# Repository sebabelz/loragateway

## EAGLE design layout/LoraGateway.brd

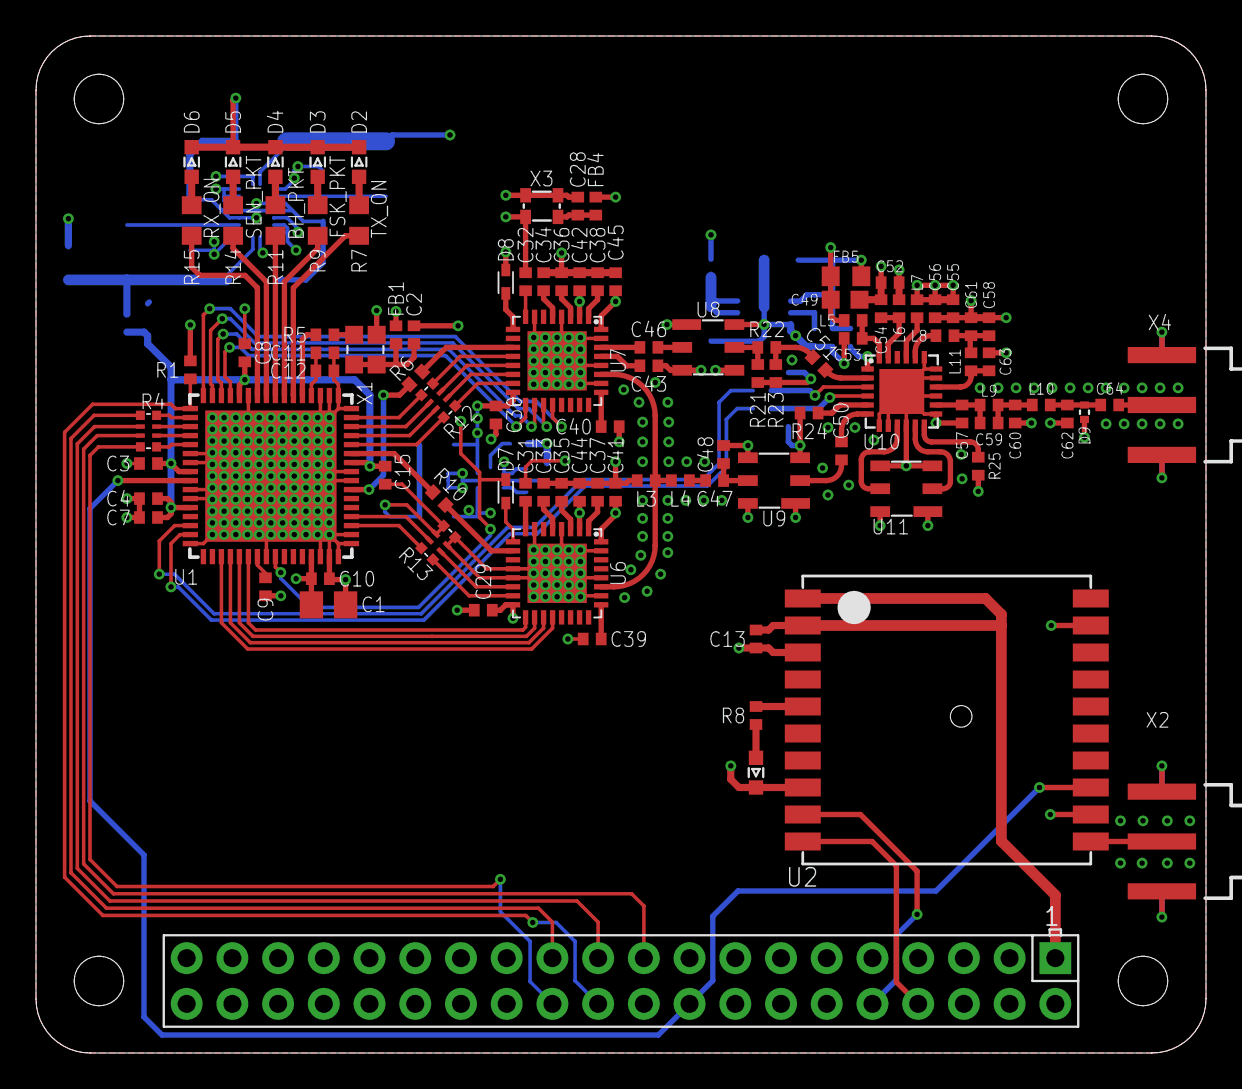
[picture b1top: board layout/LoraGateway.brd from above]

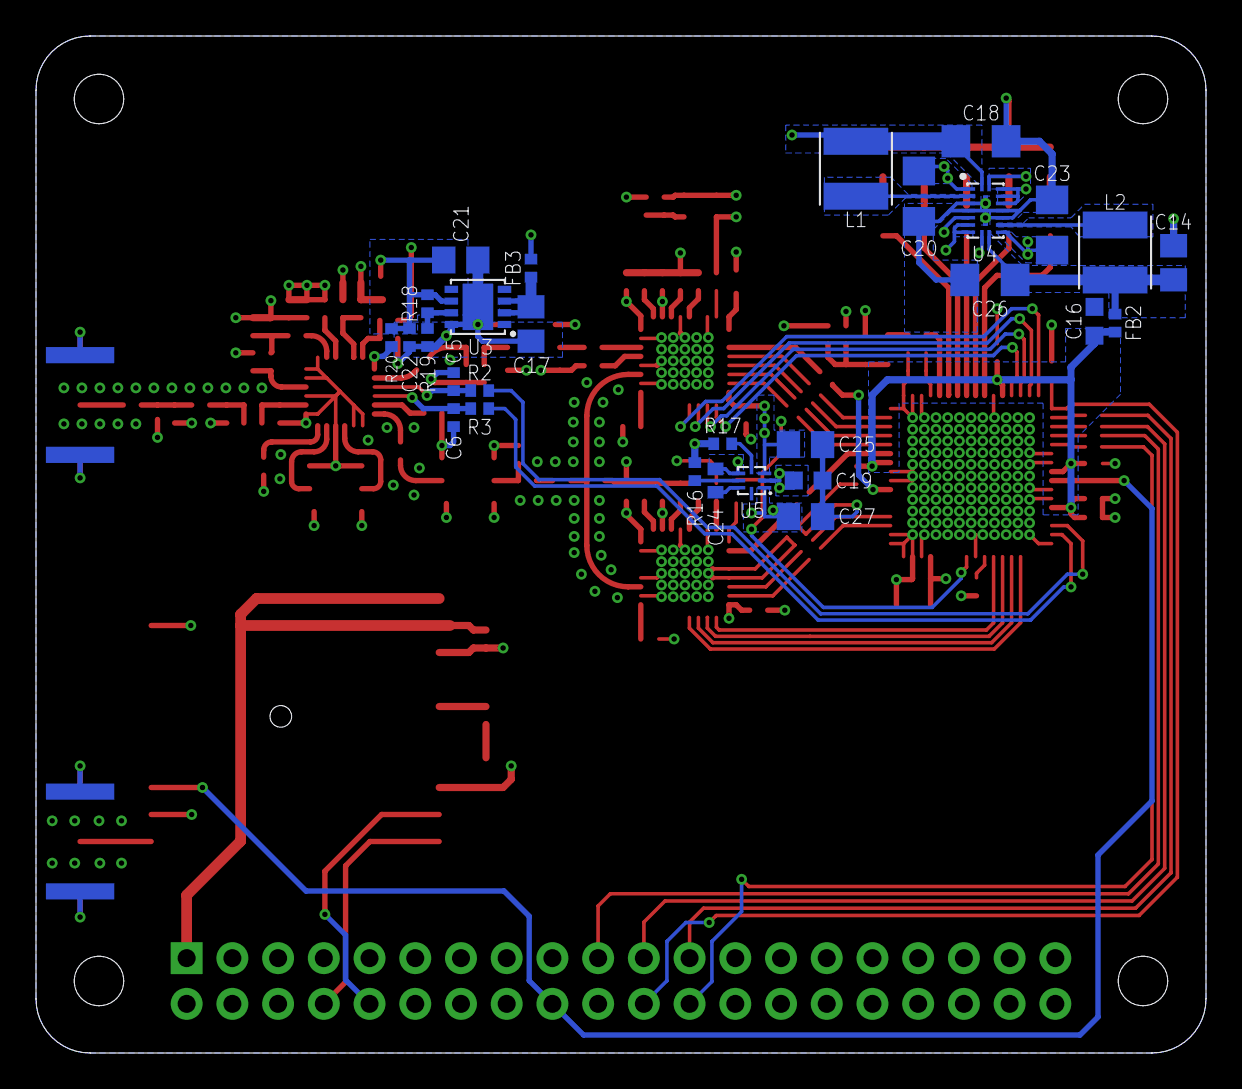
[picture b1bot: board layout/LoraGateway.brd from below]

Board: 4 copper layers, 65.0 x 56.5 mm, 130 parts (29 on the bottom side), 116 nets.

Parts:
C1, C14: 10µF; C0805
C2, C37, C38, C52: 10nF; C0402
C3, C12, C29, C30, C41, C42, C44, C45: 1µF; C0402
C4, C7, C8, C9, C10, C11, C13, C15, C24, C28, C33, C34, C35, C36, C39, C40: 100nF; C0402
C5, C6, C22, C43, C46, C47, C50, C64: 56pF; C0402
C16: 1µF; C0603
C17, C21: 10uF; C0805
C18, C26: 22uF; C1206
C19: 2.2uF; C0603
C20, C23: 10uF; C1206
C25, C27: 1uF; C0805
C31, C32, C55: 1nF; C0402
C48: 5.6pF; C0402
C49: 4.7µF; C0603
C51, C57, C60: 3.3pF; C0402
C53: 150pF; C0402
C54: 22pF; C0402
C56: 33pF; C0402
C58: 7.5pF; C0402
C59: 1.5pF; C0402
C61, C63: 5.1pF; C0402
C62: 2.7pF; C0402
D1, D2, D3, D4, D5, D6: LED; D0603
D7, D8: BAT54XV2T1G; SOD523
D9: LXES15AAA1-153
FB1, FB2, FB3, FB4: L0402
FB5: L0603
J1: RPI-HEADER3B; RPI
L1, L2: 2.2µ; ASPI-0418
L3: 33nH; L0402
L4: 3.9nH; L0402
L5: 3.3nH; L0402
L6: 4.7nH; L0402
L7: 6.8nH; L0402
L8: 2.7nH; L0402
L9, L10: 5.6nH; L0402
L11: 6.2nH; L0402
R1, R16, R17: 10k; R0402
R2, R3, R6, R10, R20: 100; R0402
R4, R12, R13: EXB-N8V101JX; EXB28V
R5: 0; R0402
R7, R9, R11, R14, R15: 470; R0603
R8: 470; R0402
R18: 16k; R0402
R19: 12k; R0402
R21, R23: 300; R0402
R22: 18; R0402
R24, R25: 49R9; R0402
U1: QFN64-9X9
U2: FGPMMOPA6H
U3: 3X3MLPD-8
U4: SC283; 2X3MLPQ-W18
U5: SC560H; MLPQ-UT8
U6, U7: SX1257; QFN32
U8, U9, U11: DCC6C-3X3
U10: SE2435L; VQFN24-4X4
X1: END4825A; 2.5X2.0MM
X2, X4: SMA-KE11; J502-ND-142-0711-871/876
X3: END4263A; 2.0X1.6MM

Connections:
+5V: C19.1, C20.1, C23.1, J1.2, J1.4, R16.1, R17.1, U4.1, U4.5, U4.8, U4.10, U4.14, U4.15, U4.16, U4.17, U5.2
CLKHS: R5.2, U1.53
CLKI: R6.2, U7.11
CLKO_B: R10.2, U6.10
FEM_EN: R20.2, U10.1
GND: C1.2, C2.2, C3.2, C4.2, C5.2, C6.2, C7.2, C8.2, C9.2, C10.2, C11.2, C12.2, C13.2, C14.2, C15.2, C16.2, C17.2, C18.2, C19.2, C20.2, C21.2, C22.2, C23.2, C24.2, C25.2, C26.2, C27.2, C28.2, C29.2, C30.2, C33.1, C34.1, C35.1, C36.1, C37.1, C38.1, C39.2, C40.2, C41.2, C42.2, C43.2, C44.2, C45.2, C48.2, C49.2, C52.2, C53.2, C54.2, C55.2, C56.2, C57.2, C58.2, C60.2, C61.2, C62.2, C63.2, D1.C, D2.C, D3.C, D4.C, D5.C, D6.C, D9.2, J1.6, J1.9, J1.14, J1.20, J1.25, J1.30, J1.34, J1.39, L3.2, R1.1, R13.1, R13.2, R13.7, R13.8, R19.1, R21.2, R23.2, R24.1, R25.1, U1.6, U1.7, U1.10, U1.11, U1.16, U1.24, U1.30, U1.31, U1.32, U1.33, U1.34, U1.40, U1.41, U1.48, U1.49, U1.50, U1.51, U1.59, U1.EXP, U2.3, U2.8, U2.12, U2.19, U3.8, U3.GND, U4.3, U4.4, U4.6, U4.7, U4.12, U4.13, U4.T1, U4.T2, U5.5, U6.4, U6.7, U6.12, U6.13, U6.26, U6.28, U6.31, U6.EXP, U7.4, U7.7, U7.26, U7.28, U7.31, U7.EXP, U8.1, U8.3, U8.4, U8.6, U9.1, U9.3, U9.4, U9.6, U10.7, U10.8, U10.10, U10.13, U10.15, U10.17, U10.18, U10.19, U10.GND, U11.1, U11.3, U11.4, U11.6, X1.2, X2.G@1, X2.G@2, X2.G@3, X2.G@4, X3.1, X3.2, X4.G@1, X4.G@2, X4.G@3, X4.G@4
GPSRX: J1.8, U2.10
GPSTX: J1.10, U2.9
IRXD_A: R12.5, U7.15
IRXD_B: R13.5, U6.15
ITXD_A: R12.7, U7.13
LNA_EN: C5.1, R2.1, U10.3
MISO_A: U1.62, U7.18
MISO_B: U1.21, U6.18
MOSI_A: U1.63, U7.19
MOSI_B: U1.20, U6.19
unnamed: L1.1, U4.2
unnamed: L2.2, U4.11
unnamed: R18.1, R19.2, U3.7
unnamed: C24.1, U5.7
unnamed: R6.1, U1.39
unnamed: R15.1, U1.58
unnamed: R11.1, U1.56
unnamed: R4.8, U1.2
unnamed: R4.7, U1.3
unnamed: C17.1, FB3.2, U3.2, U3.3
unnamed: C40.1, U7.25
unnamed: R4.6, U1.4
unnamed: R13.3, U1.36
unnamed: R5.1, X1.3
unnamed: C28.1, FB4.2, X3.4
unnamed: R25.2, U10.12
unnamed: U10.9, U11.5
unnamed: U10.11, U11.2
unnamed: R24.2, U10.5
unnamed: C54.1, L6.1, U10.23
unnamed: C58.1, C61.1, L8.1, L11.2
unnamed: C53.1, L5.1, U10.24
unnamed: L7.2, U10.21
unnamed: C59.2, C60.1, L9.1, L10.2
unnamed: R2.2, U1.14
unnamed: R3.2, U1.15
unnamed: L8.2, U10.20
unnamed: C63.1, L11.1, U10.16
unnamed: C57.1, C59.1, L9.2, U10.14
unnamed: R4.5, U1.5
unnamed: C62.1, C64.1, D9.1, L10.1
unnamed: C51.1, U10.2
unnamed: C50.2, U10.6
unnamed: C51.2, R22.1, R23.1
unnamed: C9.1, U1.23
unnamed: R21.1, R22.2, U8.5
unnamed: C46.2, U8.2
unnamed: C50.1, U9.2
unnamed: D2.A, R7.2
unnamed: C47.2, C48.1, U9.5
unnamed: C47.1, L4.1
unnamed: D3.A, R9.2
unnamed: C46.1, U7.30
unnamed: C39.1, U6.25
unnamed: D7.C, U6.9
unnamed: C31.1, U6.8
unnamed: R13.4, U1.35
unnamed: U2.11, X2.1
unnamed: C32.1, U7.8
unnamed: C38.2, U7.1
unnamed: C37.2, U6.1
unnamed: C35.2, U6.3
unnamed: C33.2, U6.5
unnamed: C36.2, U7.3
unnamed: R10.1, U1.43
unnamed: R12.4, U1.44
unnamed: R12.3, U1.45
unnamed: R12.2, U1.46
unnamed: R12.1, U1.47
unnamed: C34.2, U7.5
unnamed: C43.1, U7.29
unnamed: C64.2, X4.1
unnamed: D4.A, R11.2
unnamed: C11.1, C12.1, U1.52
unnamed: D5.A, R14.2
unnamed: D6.A, R15.2
unnamed: D8.C, U7.9
unnamed: R9.1, U1.55
unnamed: R8.2, U2.5
unnamed: D1.A, R8.1
NSS_A: U1.64, U7.20
NSS_B: U1.19, U6.20
PA_EN: C6.1, R3.1, U10.4
PPS: J1.18, U1.9, U2.13
Q1_VCC: C2.1, FB1.2, X1.1, X1.4
QRXD_A: R12.6, U7.14
QRXD_B: R13.6, U6.14
QTXD_A: R12.8, U7.12
RADIO_EN_A: R16.2, U5.6
RADIO_EN_B: R17.2, U5.4
RADIO_RST: D7.A, D8.A, U1.25
RESET: J1.22, R1.2, U1.1
RF_IN: L3.1, L4.2, U6.27, U7.27
RX_ON: R14.1, U1.57
SCK_A: U1.61, U7.17
SCK_B: U1.22, U6.17
SPI_MISO: J1.21, R4.2
SPI_MOSI: J1.19, R4.3
SPI_NSS: J1.24, R4.4
SPI_SCK: J1.23, R4.1
TX_ON: R7.1, U1.54
V+: C13.1, J1.1, U2.1, U2.2
VCC: C14.1, C26.1, FB2.1, L2.1, U4.9
VCCA_A: C25.1, C30.1, C42.1, C45.1, C52.1, FB4.1, L6.2, U5.3, U7.2, U7.16, U7.32
VCCA_B: C27.1, C29.1, C41.1, C44.1, U5.1, U6.2, U6.16, U6.32
VCCDIG18: C3.1, C4.1, C7.1, C8.1, C15.1, C16.1, FB2.2, U1.8, U1.12, U1.42, U1.60
VCCDIG33: C1.1, C10.1, C18.1, FB1.1, FB3.1, L1.2, U1.29, U4.18
VCCINT: C21.1, C22.1, FB5.1, R18.2, R20.1, U3.6
VCC_FEM: C49.1, C55.1, C56.1, FB5.2, L5.2, L7.1
XTL_OUT: C31.2, C32.2, X3.3

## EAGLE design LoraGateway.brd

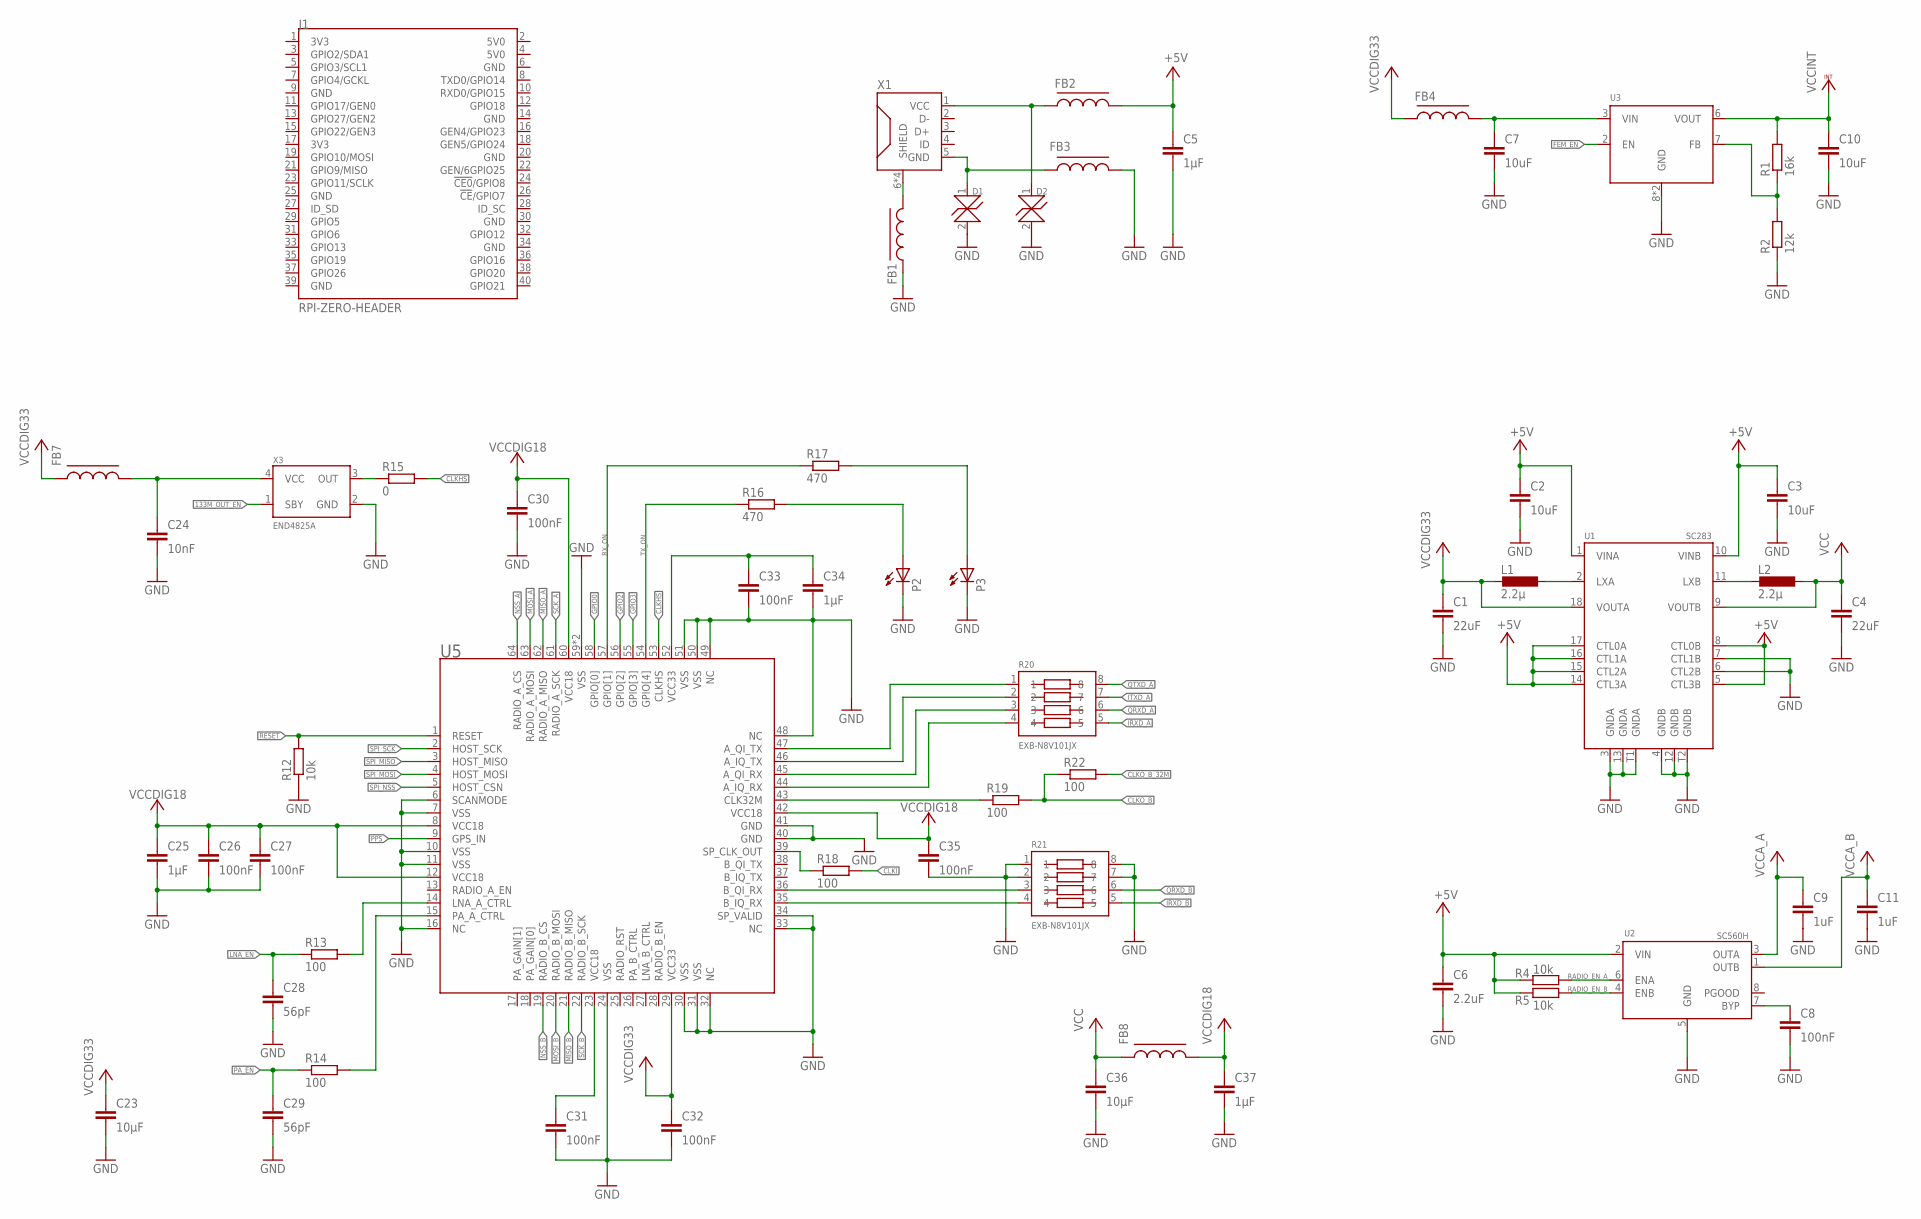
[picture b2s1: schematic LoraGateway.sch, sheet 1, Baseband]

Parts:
C1, C4: 22uF; C1206
C2, C3: 10uF; C1206
C5: 1µF; C0805
C6: 2.2uF; C0603
C7, C10: 10uF; C0805
C8, C26, C27, C30, C31, C32, C33, C35: 100nF; C0402
C9, C11: 1uF; C0805
C23, C36: 10µF; C0805
C24: 10nF; C0402
C25, C34, C37: 1µF; C0603
C28, C29: 56pF; C0402
D1, D2: RCLAMP0531T; SLP1006P2T
FB1, FB2, FB3, FB4, FB7, FB8: BLM15PG100SN1D0402; L0402
J1: RPI-ZERO-HEADER; RPI-ZERO
L1, L2: 2.2µ; ASPI-0418
P2, P3: LTST-C930KGKT
R1: 16k; R0402
R2: 12k; R0402
R4, R5, R12: 10k; R0402
R13, R14, R18, R19, R22: 100; R0402
R15: 0; R0402
R16, R17: 470; R0402
R20, R21: EXB-N8V101JX; EXB28V
U1: SC283; 2X3MLPQ-W18
U2: SC560H; MLPQ-UT8
U3: SC4212; 3X3MLPD-8
U5: SX1308; QFN64-9X9
X1: USB2-MICRO; USB-2-MICRO
X3: END4825A; 2.5X2.0MM

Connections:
133M_OUT_EN: X3.1 (SBY)
+5V: C2.1, C3.1, C5.2, C6.1, FB2.2, R4.1, R5.1, U1.1 (VINA), U1.5 (CTL3B), U1.8 (CTL0B), U1.10 (VINB), U1.14 (CTL3A), U1.15 (CTL2A), U1.16 (CTL1A), U1.17 (CTL0A), U2.2 (VIN)
CLKHS: R15.2, U5.53 (CLKHS)
CLKI: R18.2; also elsewhere on the board
CLKO_B: R19.2, R22.1; also elsewhere on the board
CLKO_B_32M: R22.2
FEM_EN: U3.2 (EN); also elsewhere on the board
GND: C1.2, C2.2, C3.2, C4.2, C5.1, C6.2, C7.2, C8.2, C9.2, C10.2, C11.2, C23.2, C24.2, C25.2, C26.2, C27.2, C28.2, C29.2, C30.2, C31.2, C32.2, C33.2, C34.2, C35.2, C36.2, C37.2, D1.2, D2.2, FB1.1, FB3.2, P2.2 (C), P3.2 (C), R2.1, R12.1, R21.1, R21.2, R21.7, R21.8, U1.3 (GNDA), U1.4 (GNDB), U1.6 (CTL2B), U1.7 (CTL1B), U1.12 (GNDB), U1.13 (GNDA), U1.T1 (GNDA), U1.T2 (GNDB), U2.5 (GND), U3.8 (GND), U3.GND, U5.6 (SCANMODE), U5.7 (VSS), U5.10 (VSS), U5.11 (VSS), U5.16 (NC), U5.24 (VSS), U5.30 (VSS), U5.31 (VSS), U5.32 (NC), U5.33 (NC), U5.34 (SP_VALID), U5.40 (GND), U5.41 (GND), U5.48 (NC), U5.49 (NC), U5.50 (VSS), U5.51 (VSS), U5.59 (VSS), U5.EXP (VSS), X3.2 (GND); also elsewhere on the board
GPIO0: U5.58 (GPIO[0])
GPIO2: U5.56 (GPIO[2])
GPIO3: U5.55 (GPIO[3])
IRXD_A: R20.5; also elsewhere on the board
IRXD_B: R21.5; also elsewhere on the board
ITXD_A: R20.7; also elsewhere on the board
LNA_EN: C28.1, R13.1; also elsewhere on the board
MISO_A: U5.62 (RADIO_A_MISO); also elsewhere on the board
MISO_B: U5.21 (RADIO_B_MISO); also elsewhere on the board
MOSI_A: U5.63 (RADIO_A_MOSI); also elsewhere on the board
MOSI_B: U5.20 (RADIO_B_MOSI); also elsewhere on the board
unnamed: L1.1, U1.2 (LXA)
unnamed: L2.2, U1.11 (LXB)
unnamed: R1.1, R2.2, U3.7 (FB)
unnamed: C8.1, U2.7 (BYP)
unnamed: D1.1, FB3.1, X1.5 (GND)
unnamed: FB1.2, X1.6 (SHIELD), X1.7 (SHIELD), X1.8 (SHIELD), X1.9 (SHIELD)
unnamed: C7.1, FB4.2, U3.3 (VIN)
unnamed: P2.1 (A), R16.2
unnamed: P3.1 (A), R17.2
unnamed: C24.1, FB7.2, X3.4 (VCC)
unnamed: R15.1, X3.3 (OUT)
unnamed: R13.2, U5.14 (LNA_A_CTRL)
unnamed: R14.2, U5.15 (PA_A_CTRL)
unnamed: C31.1, U5.23 (VCC18)
unnamed: R18.1, U5.39 (SP_CLK_OUT)
unnamed: R21.3, U5.36 (B_QI_RX)
unnamed: R21.4, U5.35 (B_IQ_RX)
unnamed: R19.1, U5.43 (CLK32M)
unnamed: R20.4, U5.44 (A_IQ_RX)
unnamed: R20.3, U5.45 (A_QI_RX)
unnamed: R20.2, U5.46 (A_IQ_TX)
unnamed: R20.1, U5.47 (A_QI_TX)
unnamed: C33.1, C34.1, U5.52 (VCC33)
NSS_A: U5.64 (RADIO_A_CS); also elsewhere on the board
NSS_B: U5.19 (RADIO_B_CS); also elsewhere on the board
PA_EN: C29.1, R14.1; also elsewhere on the board
PPS: U5.9 (GPS_IN)
QRXD_A: R20.6; also elsewhere on the board
QRXD_B: R21.6; also elsewhere on the board
QTXD_A: R20.8; also elsewhere on the board
RADIO_EN_A: R4.2, U2.6 (ENA)
RADIO_EN_B: R5.2, U2.4 (ENB)
RESET: R12.2, U5.1 (RESET)
RX_ON: R17.1, U5.57 (GPIO[1])
SCK_A: U5.61 (RADIO_A_SCK); also elsewhere on the board
SCK_B: U5.22 (RADIO_B_SCK); also elsewhere on the board
SPI_MISO: U5.3 (HOST_MISO)
SPI_MOSI: U5.4 (HOST_MOSI)
SPI_NSS: U5.5 (HOST_CSN)
SPI_SCK: U5.2 (HOST_SCK)
TX_ON: R16.1, U5.54 (GPIO[4])
VBUS: D2.1, FB2.1, X1.1 (VCC)
VCC: C4.1, C36.1, FB8.1, L2.1, U1.9 (VOUTB)
VCCA_A: C9.1, U2.3 (OUTA); also elsewhere on the board
VCCA_B: C11.1, U2.1 (OUTB); also elsewhere on the board
VCCDIG18: C25.1, C26.1, C27.1, C30.1, C35.1, C37.1, FB8.2, U5.8 (VCC18), U5.12 (VCC18), U5.42 (VCC18), U5.60 (VCC18)
VCCDIG33: C1.1, C23.1, C32.1, FB4.1, FB7.1, L1.2, U1.18 (VOUTA), U5.29 (VCC33)
VCCINT: C10.1, R1.2, U3.6 (VOUT); also elsewhere on the board

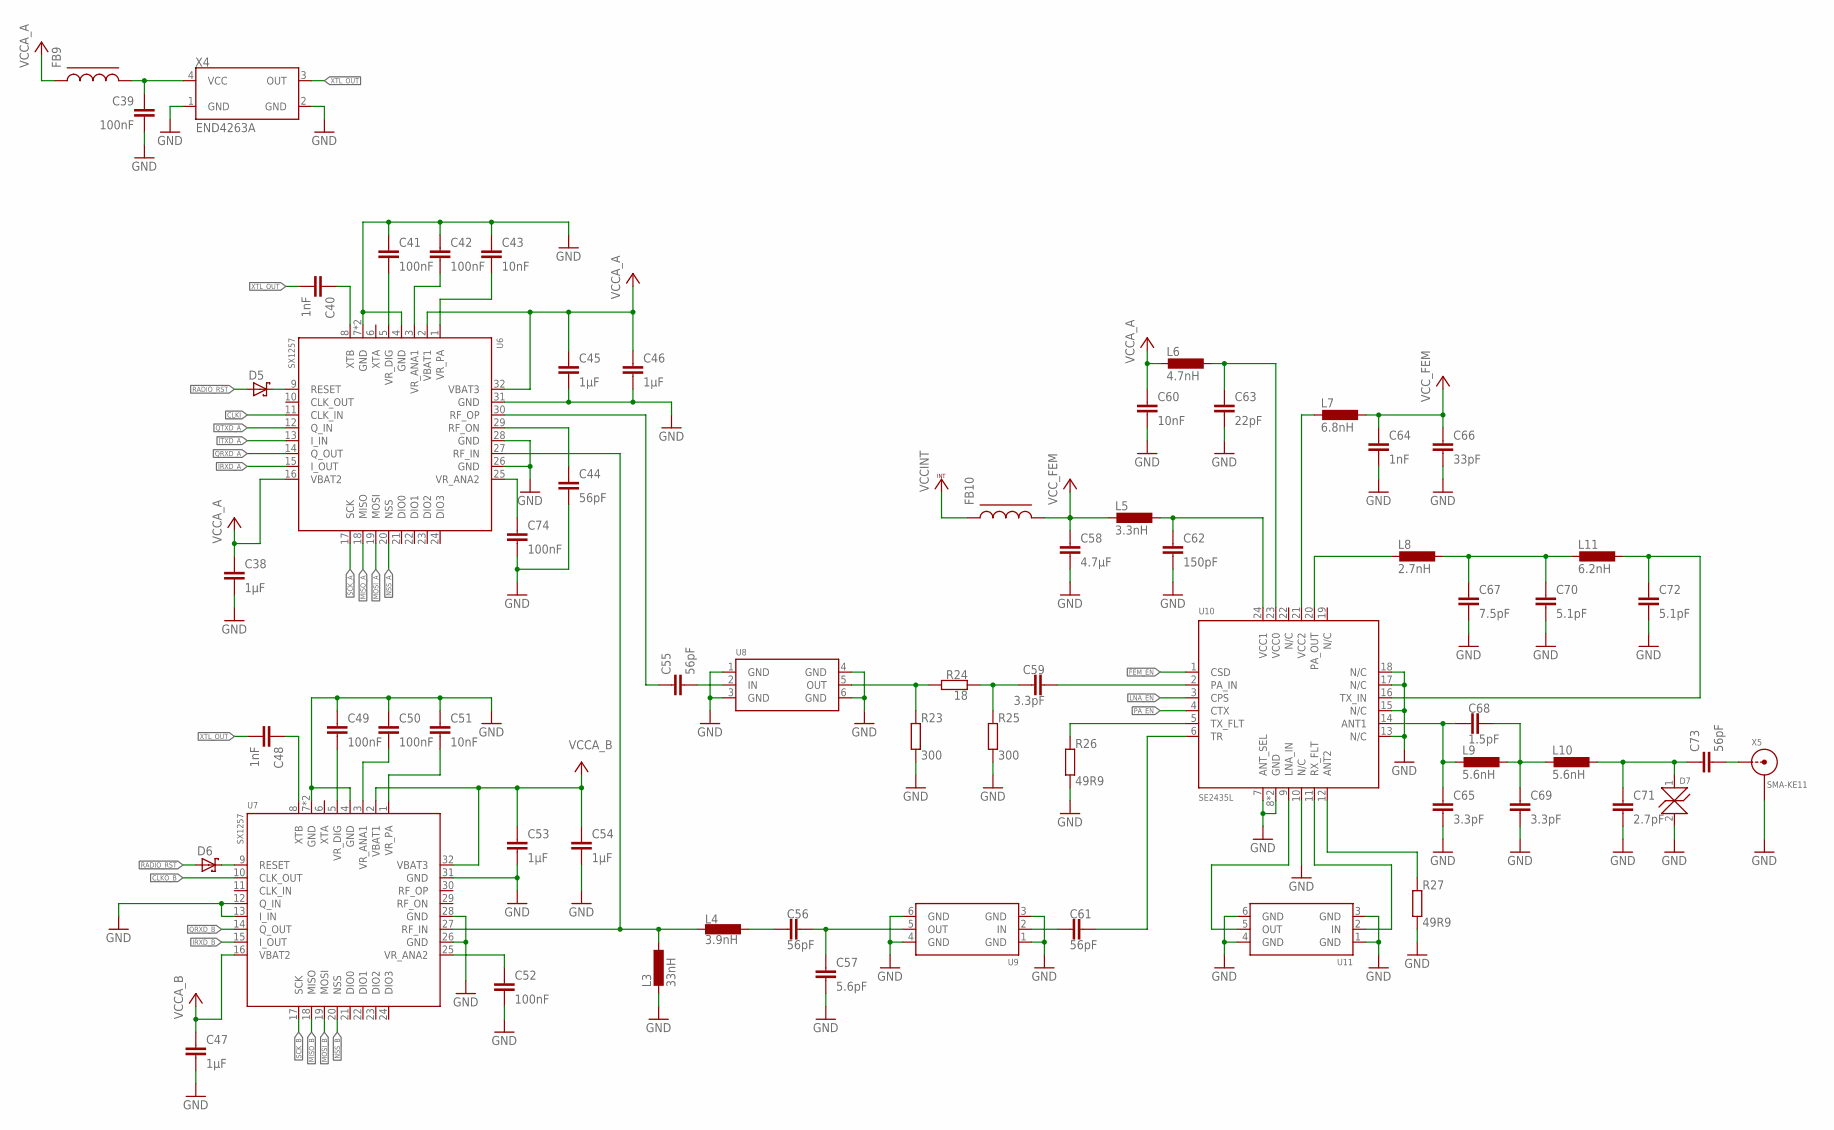
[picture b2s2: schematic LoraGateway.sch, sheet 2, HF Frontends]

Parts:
C38, C45, C46, C47, C53, C54: 1µF; C0603
C39, C41, C42, C49, C50, C52, C74: 100nF; C0402
C40, C48, C64: 1nF; C0402
C43, C51, C60: 10nF; C0402
C44, C55, C56, C61, C73: 56pF; C0402
C57: 5.6pF; C0402
C58: 4.7µF; C0603
C59, C65, C69: 3.3pF; C0402
C62: 150pF; C0402
C63: 22pF; C0402
C66: 33pF; C0402
C67: 7.5pF; C0402
C68: 1.5pF; C0402
C70, C72: 5.1pF; C0402
C71: 2.7pF; C0402
D5, D6: BAT54XV2T1G; SOD523
D7: LXES15AAA1-153
FB9: BLM15PG100SN1D0402; L0402
FB10: BLM18PG121SH1D; L0603
L3: 33nH; L0402
L4: 3.9nH; L0402
L5: 3.3nH; L0402
L6: 4.7nH; L0402
L7: 6.8nH; L0402
L8: 2.7nH; L0402
L9, L10: 5.6nH; L0402
L11: 6.2nH; L0402
R23, R25: 300; R0402
R24: 18; R0402
R26, R27: 49R9; R0402
U6, U7: SX1257; QFN32
U8, U9, U11: B39871B3717U410; DCC6C-3X3
U10: SE2435L; VQFN24-4X4
X4: END4263A; 2.0X1.6MM
X5: SMA-KE11; J502-ND-142-0711-871/876

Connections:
CLKI: U6.11 (CLK_IN); also elsewhere on the board
CLKO_B: U7.10 (CLK_OUT); also elsewhere on the board
FEM_EN: U10.1 (CSD); also elsewhere on the board
GND: C38.2, C39.2, C41.1, C42.1, C43.1, C44.2, C45.2, C46.2, C47.2, C49.1, C50.1, C51.1, C52.2, C53.2, C54.2, C57.2, C58.2, C60.2, C62.2, C63.2, C64.2, C65.2, C66.2, C67.2, C69.2, C70.2, C71.2, C72.2, C74.2, D7.2, L3.2, R23.2, R25.2, R26.1, R27.1, U6.4 (GND), U6.7 (GND), U6.26 (GND), U6.28 (GND), U6.31 (GND), U6.EXP (GND), U7.4 (GND), U7.7 (GND), U7.12 (Q_IN), U7.13 (I_IN), U7.26 (GND), U7.28 (GND), U7.31 (GND), U7.EXP (GND), U8.1 (GND), U8.3 (GND), U8.4 (GND), U8.6 (GND), U9.1 (GND), U9.3 (GND), U9.4 (GND), U9.6 (GND), U10.7 (ANT_SEL), U10.8 (GND), U10.10 (N/C), U10.13 (N/C), U10.15 (N/C), U10.17 (N/C), U10.18 (N/C), U10.GND, U11.1 (GND), U11.3 (GND), U11.4 (GND), U11.6 (GND), X4.1 (GND), X4.2 (GND), X5.G@1 (GND), X5.G@2 (GND), X5.G@3 (GND), X5.G@4 (GND); also elsewhere on the board
IRXD_A: U6.15 (I_OUT); also elsewhere on the board
IRXD_B: U7.15 (I_OUT); also elsewhere on the board
ITXD_A: U6.13 (I_IN); also elsewhere on the board
LNA_EN: U10.3 (CPS); also elsewhere on the board
MISO_A: U6.18 (MISO); also elsewhere on the board
MISO_B: U7.18 (MISO); also elsewhere on the board
MOSI_A: U6.19 (MOSI); also elsewhere on the board
MOSI_B: U7.19 (MOSI); also elsewhere on the board
unnamed: C74.1, U6.25 (VR_ANA2)
unnamed: C39.1, FB9.2, X4.4 (VCC)
unnamed: R27.2, U10.12 (ANT2)
unnamed: U10.9 (LNA_IN), U11.5 (OUT)
unnamed: U10.11 (RX_FLT), U11.2 (IN)
unnamed: R26.2, U10.5 (TX_FLT)
unnamed: C63.1, L6.1, U10.23 (VCC0)
unnamed: C67.1, C70.1, L8.1, L11.2
unnamed: C62.1, L5.1, U10.24 (VCC1)
unnamed: L7.2, U10.21 (VCC2)
unnamed: C68.2, C69.1, L9.1, L10.2
unnamed: L8.2, U10.20 (PA_OUT)
unnamed: C72.1, L11.1, U10.16 (TX_IN)
unnamed: C65.1, C68.1, L9.2, U10.14 (ANT1)
unnamed: C71.1, C73.1, D7.1, L10.1
unnamed: C59.1, U10.2 (PA_IN)
unnamed: C61.2, U10.6 (TR)
unnamed: C59.2, R24.1, R25.1
unnamed: R23.1, R24.2, U8.5 (OUT)
unnamed: C55.2, U8.2 (IN)
unnamed: C61.1, U9.2 (IN)
unnamed: C56.2, C57.1, U9.5 (OUT)
unnamed: C56.1, L4.1
unnamed: C55.1, U6.30 (RF_OP)
unnamed: C52.1, U7.25 (VR_ANA2)
unnamed: D6.C, U7.9 (RESET)
unnamed: C48.1, U7.8 (XTB)
unnamed: C40.1, U6.8 (XTB)
unnamed: C43.2, U6.1 (VR_PA)
unnamed: C51.2, U7.1 (VR_PA)
unnamed: C50.2, U7.3 (VR_ANA1)
unnamed: C49.2, U7.5 (VR_DIG)
unnamed: C42.2, U6.3 (VR_ANA1)
unnamed: C41.2, U6.5 (VR_DIG)
unnamed: C44.1, U6.29 (RF_ON)
unnamed: C73.2, X5.1
unnamed: D5.C, U6.9 (RESET)
NSS_A: U6.20 (NSS); also elsewhere on the board
NSS_B: U7.20 (NSS); also elsewhere on the board
PA_EN: U10.4 (CTX); also elsewhere on the board
QRXD_A: U6.14 (Q_OUT); also elsewhere on the board
QRXD_B: U7.14 (Q_OUT); also elsewhere on the board
QTXD_A: U6.12 (Q_IN); also elsewhere on the board
RADIO_RST: D5.A, D6.A
RF_IN: L3.1, L4.2, U6.27 (RF_IN), U7.27 (RF_IN)
SCK_A: U6.17 (SCK); also elsewhere on the board
SCK_B: U7.17 (SCK); also elsewhere on the board
VCCA_A: C38.1, C45.1, C46.1, C60.1, FB9.1, L6.2, U6.2 (VBAT1), U6.16 (VBAT2), U6.32 (VBAT3); also elsewhere on the board
VCCA_B: C47.1, C53.1, C54.1, U7.2 (VBAT1), U7.16 (VBAT2), U7.32 (VBAT3); also elsewhere on the board
VCCINT: FB10.1; also elsewhere on the board
VCC_FEM: C58.1, C64.1, C66.1, FB10.2, L5.2, L7.1
XTL_OUT: C40.2, C48.2, X4.3 (OUT)

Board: 4 copper layers, 124 parts (27 on the bottom side), 98 nets, no tracks yet.

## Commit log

2019-01-18 Initial Commit of lora gateway
2019-01-18 old layout removed, Rpi-Zero Header added
2019-01-18 eagle project created
2019-01-24 Rpi-shield
2019-01-24 gps modul connected
2019-10-11 gateway routed
